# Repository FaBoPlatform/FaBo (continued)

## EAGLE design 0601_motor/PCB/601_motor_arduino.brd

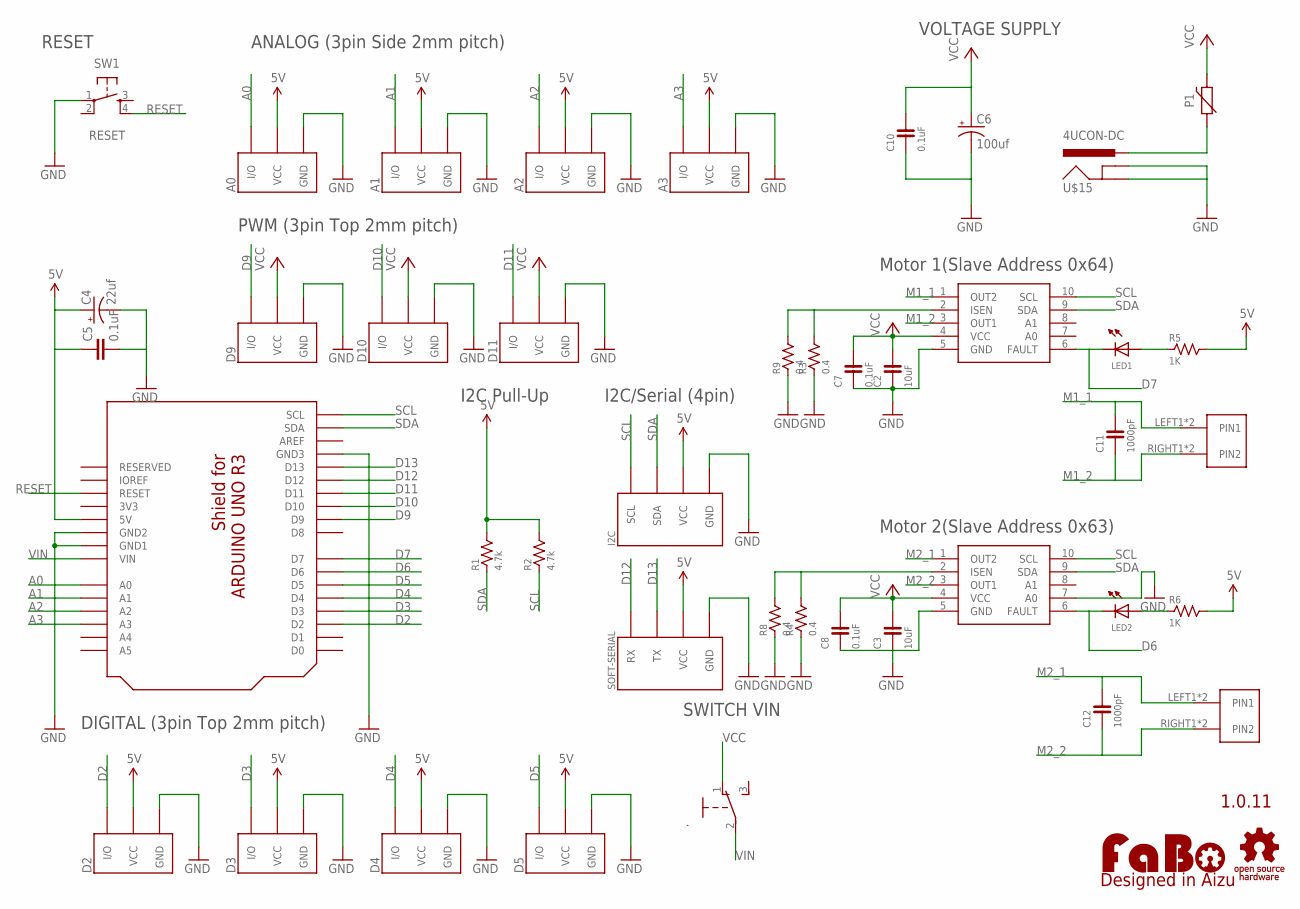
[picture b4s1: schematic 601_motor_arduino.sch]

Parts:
.: SLIDE-EG1218; EG1218
A0, A1, A2, A3: FABO_BRICK_3PIN-S03B-PASK-2; FABO_BRICK_3PIN_S03B-PASK-2
C2, C3: 10uF; 0603
C4: 22uf; 153CLV-0405
C5: 0.1uF; EIA0603
C6: 100uf; 153CLV-0405
C7, C8, C10: 0.1uF; 0603
C11, C12: 1000pF; 0603
D2, D3, D4, D5: FABO_BRICK_3PIN-B03B-PASK-1; FABO_BRICK_3PIN_B03B-PASK-1
D9, D10, D11: FABO_BRICK_3PIN-HEADER; FABO_BRICK_3PIN_HEADER
I2C: FABO_BRICK_I2C-S04B-PASK-2; FABO_BRICK_I2C_S04B-PASK-2
LED1, LED2: LED-0603; 0603
LOGO1: LOGO_FABO-M; LOGO_FABO_M
P1: POLYSWITCHMF-NSML1; 1206
R1, R2: 4.7k; 0603
R3, R4, R8, R9: 0.4; 0603
R5, R6: 1K; 0603
SOFT-SERIAL: FABO_BRICK_SERIAL-S04B-PASK-2; FABO_BRICK_SERIAL_S04B-PASK-2
SW1: RESET; DTS_6_V
U1: ARDUINO_UNO_R3_SHIELD-NOLABEL; ARDUINO_UNO_R3_NOLABEL
U$6: LOGO_OSHW-T_M; LOGO_OSHW_T_MS
U$8, U$10: DRV8830
U$12, U$13: ML-1400-S1
U$15: 4UCON-DC

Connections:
3V3: U1.3V3
5V: A0.VCC, A1.VCC, A2.VCC, A3.VCC, C4.+, C5.1, D2.VCC, D3.VCC, D4.VCC, D5.VCC, I2C.VCC, R1.2, R2.2, R5.2, R6.2, SOFT-SERIAL.VCC, U1.5V
A0: A0.I/O, U1.A0
A1: A1.I/O, U1.A1
A2: A2.I/O, U1.A2
A3: A3.I/O, U1.A3
D2: D2.I/O, U1.D2
D3: D3.I/O, U1.D3
D4: D4.I/O, U1.D4
D5: D5.I/O, U1.D5
D6: LED2.CATHODE, U1.D6, U$10.6 (FAULT)
D7: LED1.CATHODE, U1.D7, U$8.6 (FAULT)
D9: D9.I/O, U1.D9
D10: D10.I/O, U1.D10
D11: D11.I/O, U1.D11
D12: SOFT-SERIAL.RX, U1.D12
D13: SOFT-SERIAL.TX, U1.D13
GND: A0.GND, A1.GND, A2.GND, A3.GND, C2.1, C3.1, C4.-, C5.2, C6.-, C7.1, C8.1, C10.1, D2.GND, D3.GND, D4.GND, D5.GND, D9.GND, D10.GND, D11.GND, I2C.GND, R3.1, R4.1, R8.1, R9.1, SOFT-SERIAL.GND, SW1.1, U1.GND1, U1.GND2, U1.GND3, U$8.5 (GND), U$10.5 (GND), U$10.7 (A0), U$15.GND1 (GND), U$15.GND2 (GNDBREAK)
M1_1: C11.2, U$8.1 (OUT2), U$12.LEFT1 (PIN1), U$12.LEFT2 (PIN1)
M1_2: C11.1, U$8.3 (OUT1), U$12.RIGHT1 (PIN2), U$12.RIGHT2 (PIN2)
M2_1: C12.2, U$10.1 (OUT2), U$13.LEFT1 (PIN1), U$13.LEFT2 (PIN1)
M2_2: C12.1, U$10.3 (OUT1), U$13.RIGHT1 (PIN2), U$13.RIGHT2 (PIN2)
unnamed: P1.P$1 (1), U$15.VCC (PWR)
unnamed: R3.2, R9.2, U$8.2 (ISEN)
unnamed: R4.2, R8.2, U$10.2 (ISEN)
unnamed: LED1.ANODE, R5.1
unnamed: LED2.ANODE, R6.1
RESET: SW1.4, U1.RESET
SCL: I2C.SCL, R2.1, U1.SCL, U$8.10 (SCL), U$10.10 (SCL)
SDA: I2C.SDA, R1.1, U1.SDA, U$8.9 (SDA), U$10.9 (SDA)
VCC: ..1, C2.2, C3.2, C6.+, C7.2, C8.2, C10.2, D9.VCC, D10.VCC, D11.VCC, P1.P$2 (2), U$8.4 (VCC), U$10.4 (VCC)
VIN: ..2, U1.VIN

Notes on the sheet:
1.0.11
I2C/Serial (4pin)
PWM (3pin Top 2mm pitch)
ANALOG (3pin Side 2mm pitch)
I2C Pull-Up
VOLTAGE SUPPLY
DIGITAL (3pin Top 2mm pitch)
RESET
Motor 1(Slave Address 0x64)
Motor 2(Slave Address 0x63)
SWITCH VIN

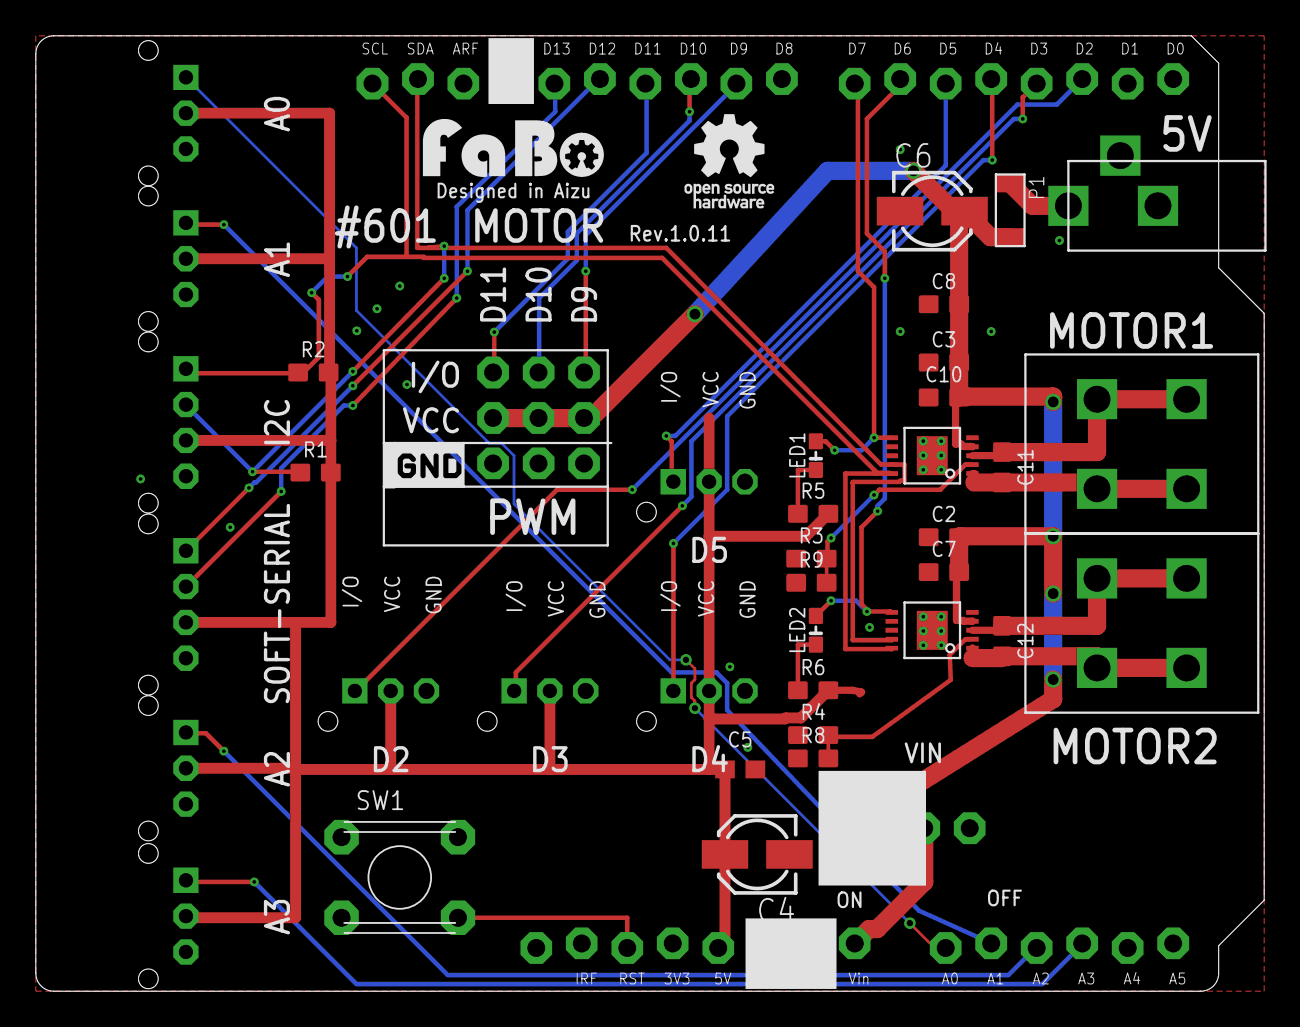
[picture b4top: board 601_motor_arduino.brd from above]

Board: 2 copper layers, 68.6 x 53.3 mm, 45 parts (0 on the bottom side), 31 nets.

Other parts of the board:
U$19: LOGO_SILK_GND

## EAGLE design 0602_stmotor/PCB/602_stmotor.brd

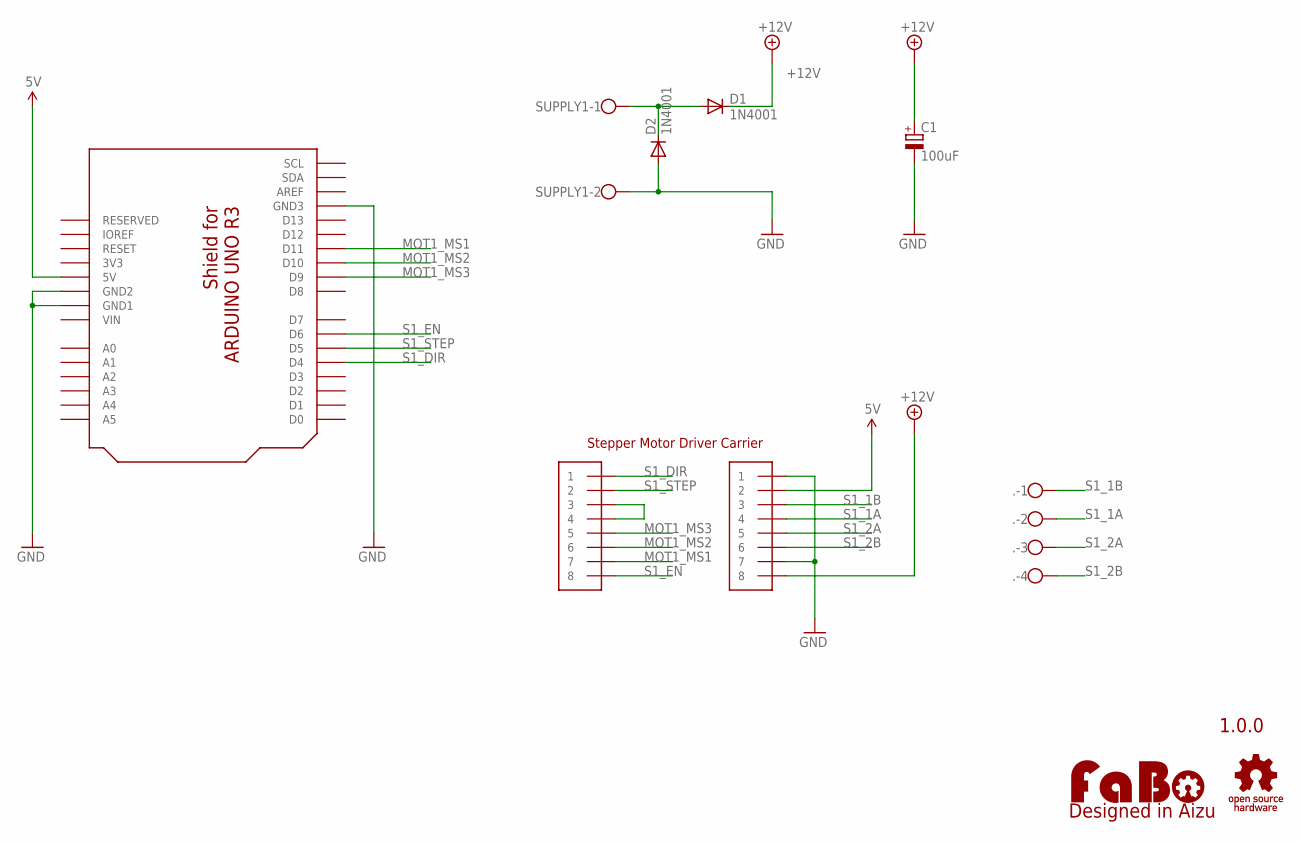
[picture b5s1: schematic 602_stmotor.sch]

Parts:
.: W237-4
C1: 100uF; 153CLV-0807
CN1, CN2: PIN_HEADER_1X8-LONG; PIN_1X8_LONG
D1, D2: 1N4001; DO41-10
LOGO1: LOGO_FABO-M; LOGO_FABO_M
SUPPLY1: W237-102
U1: ARDUINO_UNO_R3_SHIELD-NOLABEL; ARDUINO_UNO_R3_NOLABEL
U$2: LOGO_OSHW-T_M; LOGO_OSHW_T_MS

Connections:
3V3: U1.3V3
5V: CN2.2, U1.5V
+12V: C1.+, CN2.8, D1.C
GND: C1.-, CN2.1, CN2.7, D2.A, SUPPLY1.2, U1.GND1, U1.GND2, U1.GND3
MOT1_MS1: CN1.7, U1.D11
MOT1_MS2: CN1.6, U1.D10
MOT1_MS3: CN1.5, U1.D9
unnamed: D1.A, D2.C, SUPPLY1.1
unnamed: CN1.3, CN1.4
S1_1A: ..2, CN2.4
S1_1B: ..1, CN2.3
S1_2A: ..3, CN2.5
S1_2B: ..4, CN2.6
S1_DIR: CN1.1, U1.D4
S1_EN: CN1.8, U1.D6
S1_STEP: CN1.2, U1.D5
VIN: U1.VIN

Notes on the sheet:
1.0.0
Stepper Motor Driver Carrier

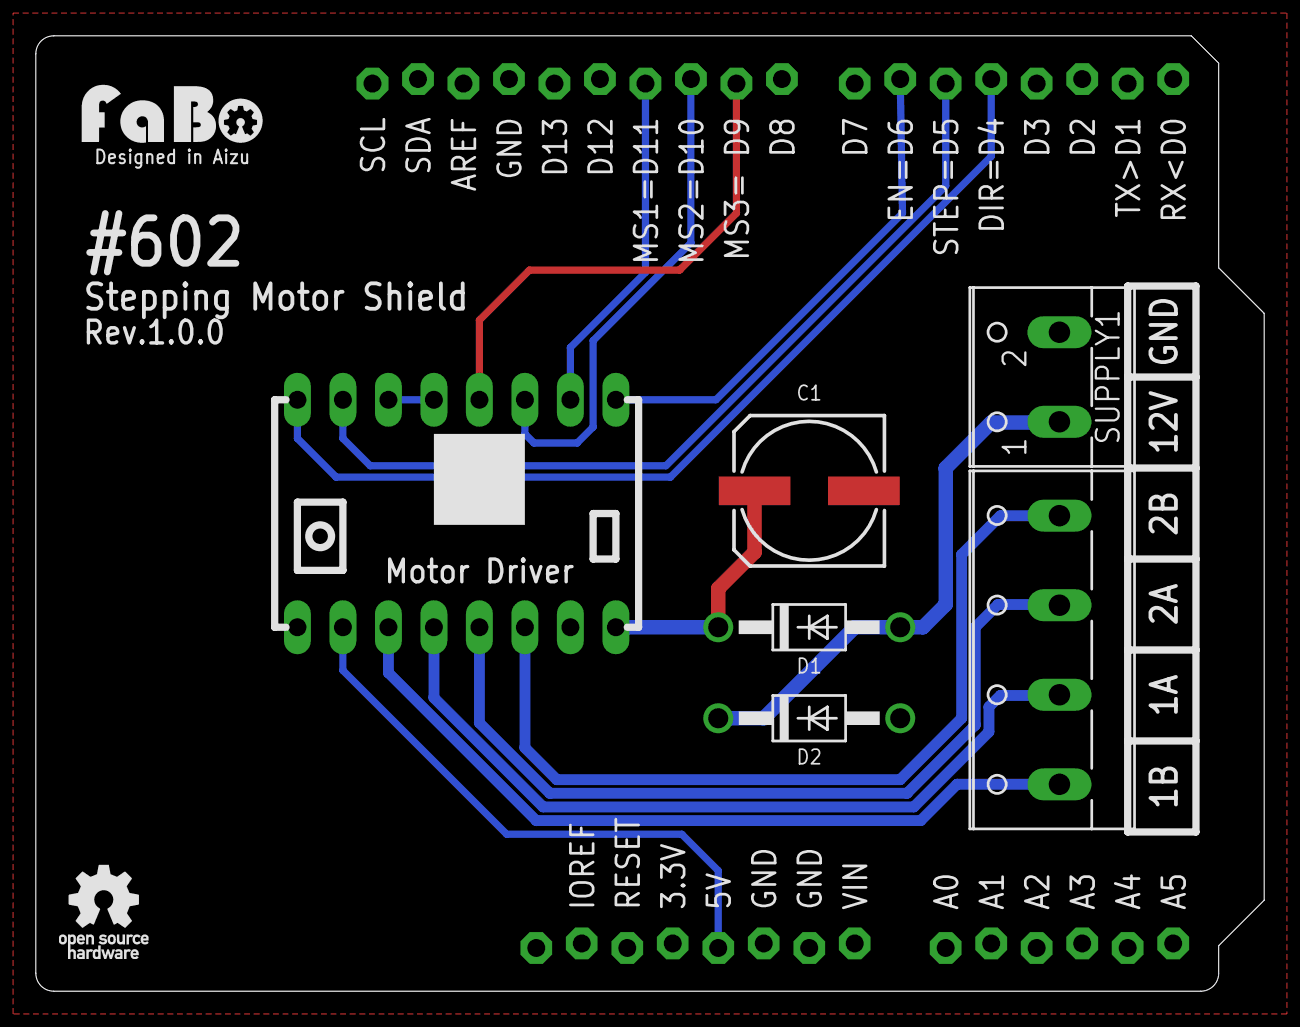
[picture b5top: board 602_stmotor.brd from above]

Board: 2 copper layers, 68.6 x 53.3 mm, 10 parts (0 on the bottom side), 15 nets.

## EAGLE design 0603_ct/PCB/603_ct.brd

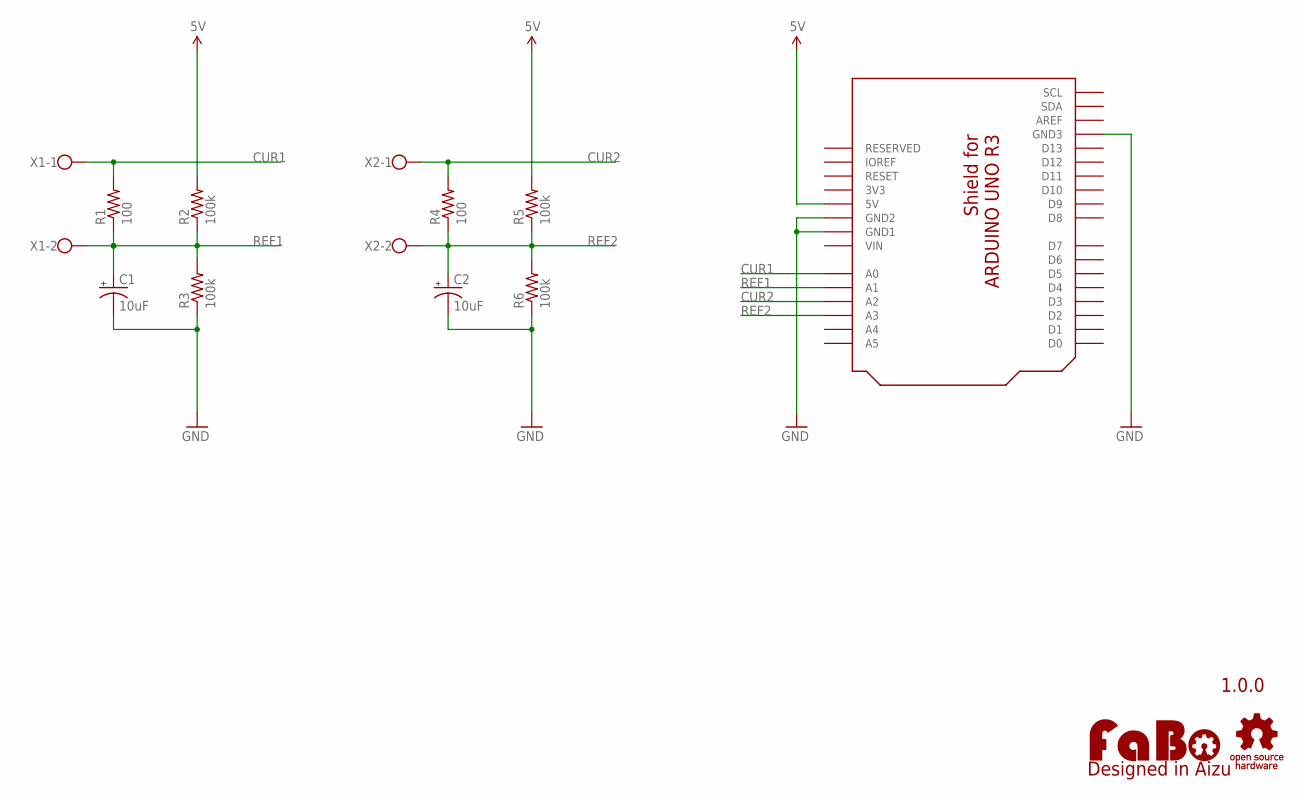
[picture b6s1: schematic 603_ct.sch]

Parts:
C1, C2: 10uF; CAP-POL-AXL-5MM
LOGO1: LOGO_FABO-M; LOGO_FABO_M
R1, R4: 100; RES-AXL-REGULAR
R2, R3, R5, R6: 100k; RES-AXL-REGULAR
U2: ARDUINO_UNO_R3_SHIELD-NOLABEL; ARDUINO_UNO_R3_NOLABEL
U$2: LOGO_OSHW-T_M; LOGO_OSHW_T_MS
X1, X2: W237-102

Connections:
3V3: U2.3V3
5V: R2.P$2 (2), R5.P$2 (2), U2.5V
CUR1: R1.P$2 (2), U2.A0, X1.1
CUR2: R4.P$2 (2), U2.A2, X2.1
GND: C1.-, C2.-, R3.P$1 (1), R6.P$1 (1), U2.GND1, U2.GND2, U2.GND3
REF1: C1.+, R1.P$1 (1), R2.P$1 (1), R3.P$2 (2), U2.A1, X1.2
REF2: C2.+, R4.P$1 (1), R5.P$1 (1), R6.P$2 (2), U2.A3, X2.2
VIN: U2.VIN

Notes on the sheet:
1.0.0

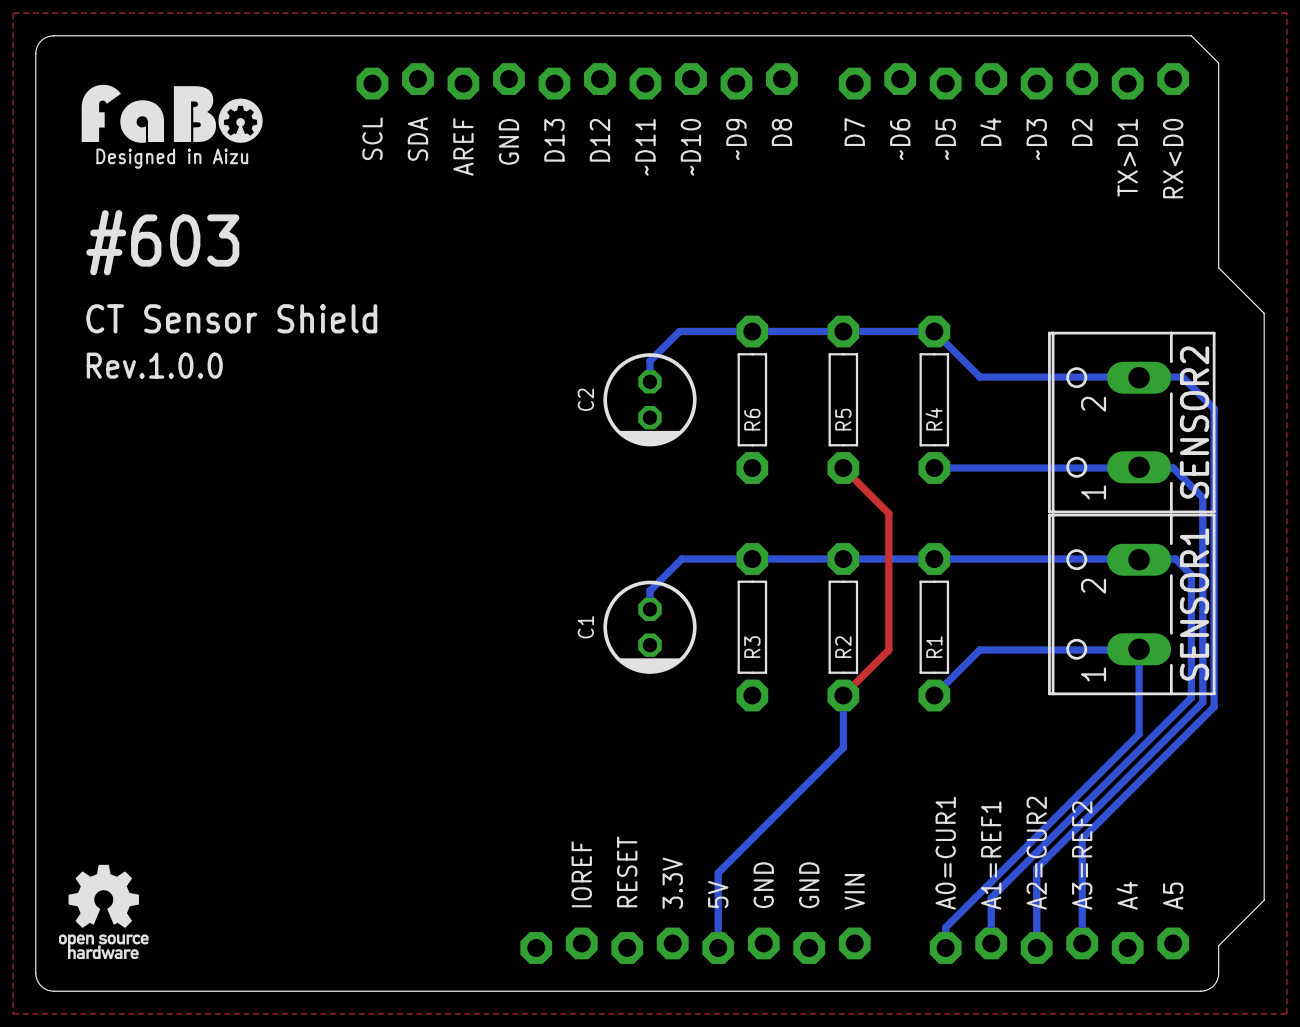
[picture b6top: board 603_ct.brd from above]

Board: 2 copper layers, 68.6 x 53.3 mm, 13 parts (0 on the bottom side), 6 nets.

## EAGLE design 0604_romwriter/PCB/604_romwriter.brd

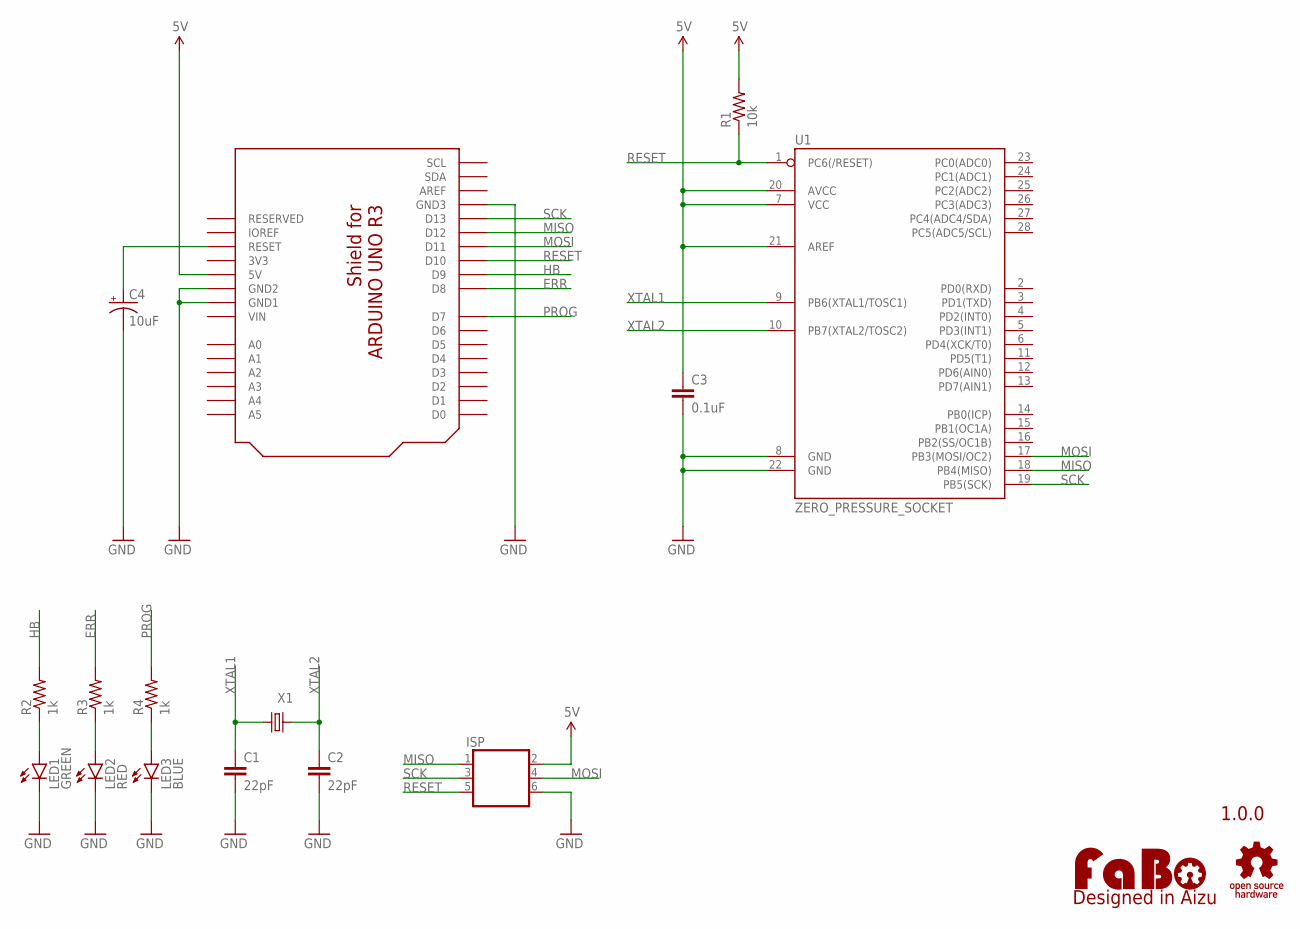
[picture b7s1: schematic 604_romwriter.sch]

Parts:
C1, C2: 22pF; CAP-PTH-SMALL
C3: 0.1uF; CAP-PTH-SMALL
C4: 10uF; CAP-POL-AXL-5MM
ISP: PINHEAD_2X3; PIN_2X3
LED1: GREEN; LED-5MM
LED2: RED; LED-5MM
LED3: BLUE; LED-5MM
LOGO1: LOGO_FABO-M; LOGO_FABO_M
R1: 10k; RES-AXL-REGULAR
R2, R3, R4: 1k; RES-AXL-REGULAR
U1: ZERO_PRESSURE_SOCKET; ZERO_PRESSURE_SOCKET_DIL28
U2: ARDUINO_UNO_R3_SHIELD-NOLABEL; ARDUINO_UNO_R3_NOLABEL
U$2: LOGO_OSHW-T_M; LOGO_OSHW_T_MS
X1: CRYSTAL; RESONATOR_PTH

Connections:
3V3: U2.3V3
5V: C3.1, ISP.2, R1.P$2 (2), U1.7 (VCC), U1.20 (AVCC), U1.21 (AREF), U2.5V
ERR: R3.P$2 (2), U2.D8
GND: C1.2, C2.2, C3.2, C4.-, ISP.6, LED1.K (C), LED2.K (C), LED3.K (C), U1.8 (GND), U1.22 (GND), U2.GND1, U2.GND2, U2.GND3
HB: R2.P$2 (2), U2.D9
MISO: ISP.1, U1.18 (PB4(MISO)), U2.D12
MOSI: ISP.4, U1.17 (PB3(MOSI/OC2)), U2.D11
unnamed: C4.+, U2.RESET
unnamed: LED1.A, R2.P$1 (1)
unnamed: LED2.A, R3.P$1 (1)
unnamed: LED3.A, R4.P$1 (1)
PROG: R4.P$2 (2), U2.D7
RESET: ISP.5, R1.P$1 (1), U1.1 (PC6(/RESET)), U2.D10
SCK: ISP.3, U1.19 (PB5(SCK)), U2.D13
VIN: U2.VIN
XTAL1: C1.1, U1.9 (PB6(XTAL1/TOSC1)), X1.1
XTAL2: C2.1, U1.10 (PB7(XTAL2/TOSC2)), X1.2

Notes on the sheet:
1.0.0

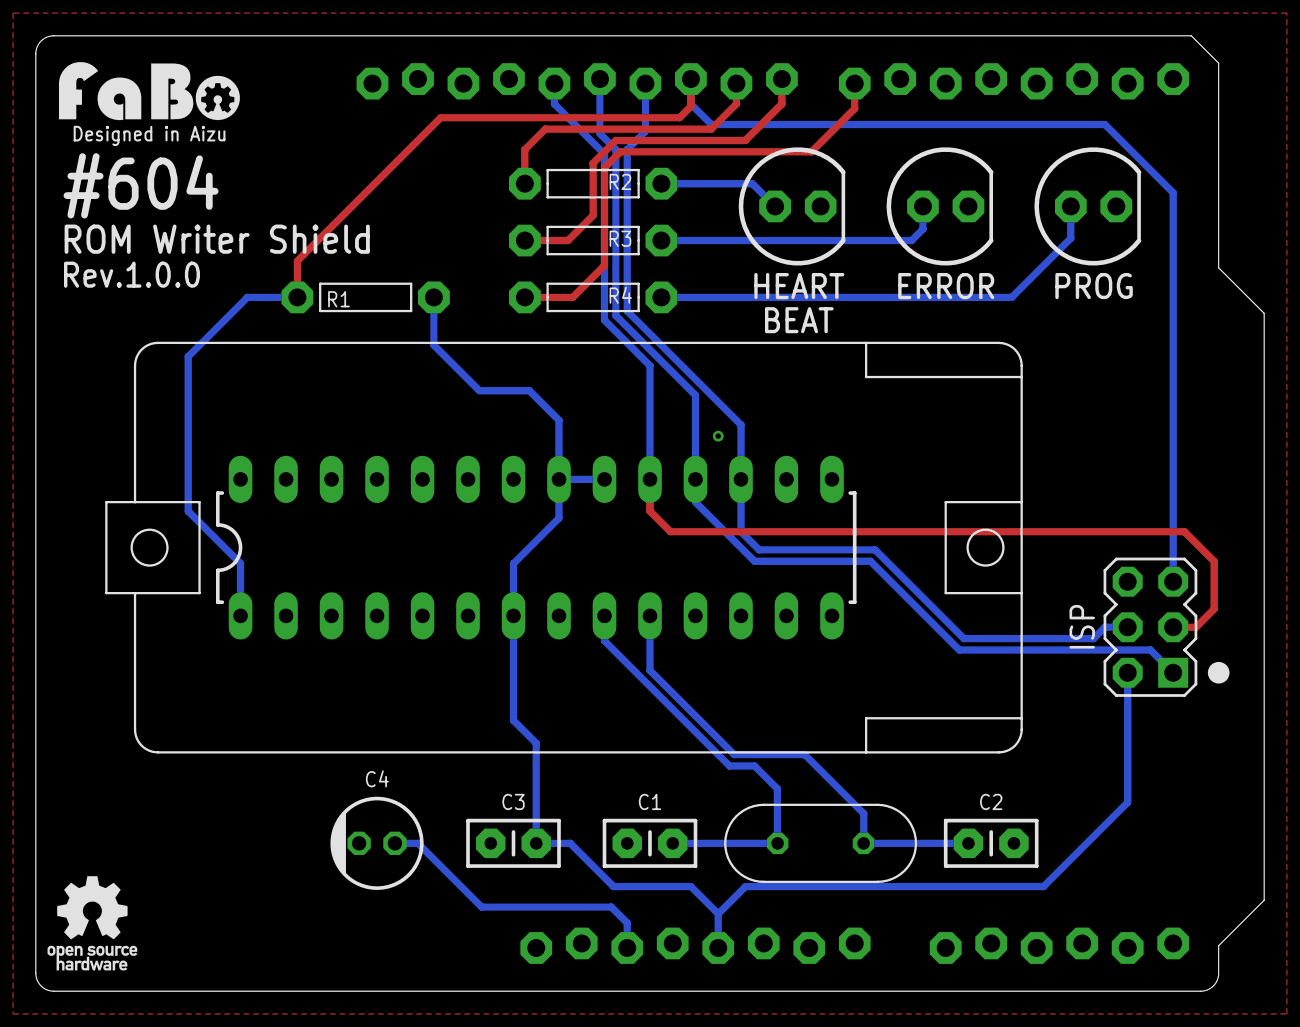
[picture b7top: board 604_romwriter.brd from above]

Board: 2 copper layers, 68.6 x 53.3 mm, 17 parts (0 on the bottom side), 15 nets.

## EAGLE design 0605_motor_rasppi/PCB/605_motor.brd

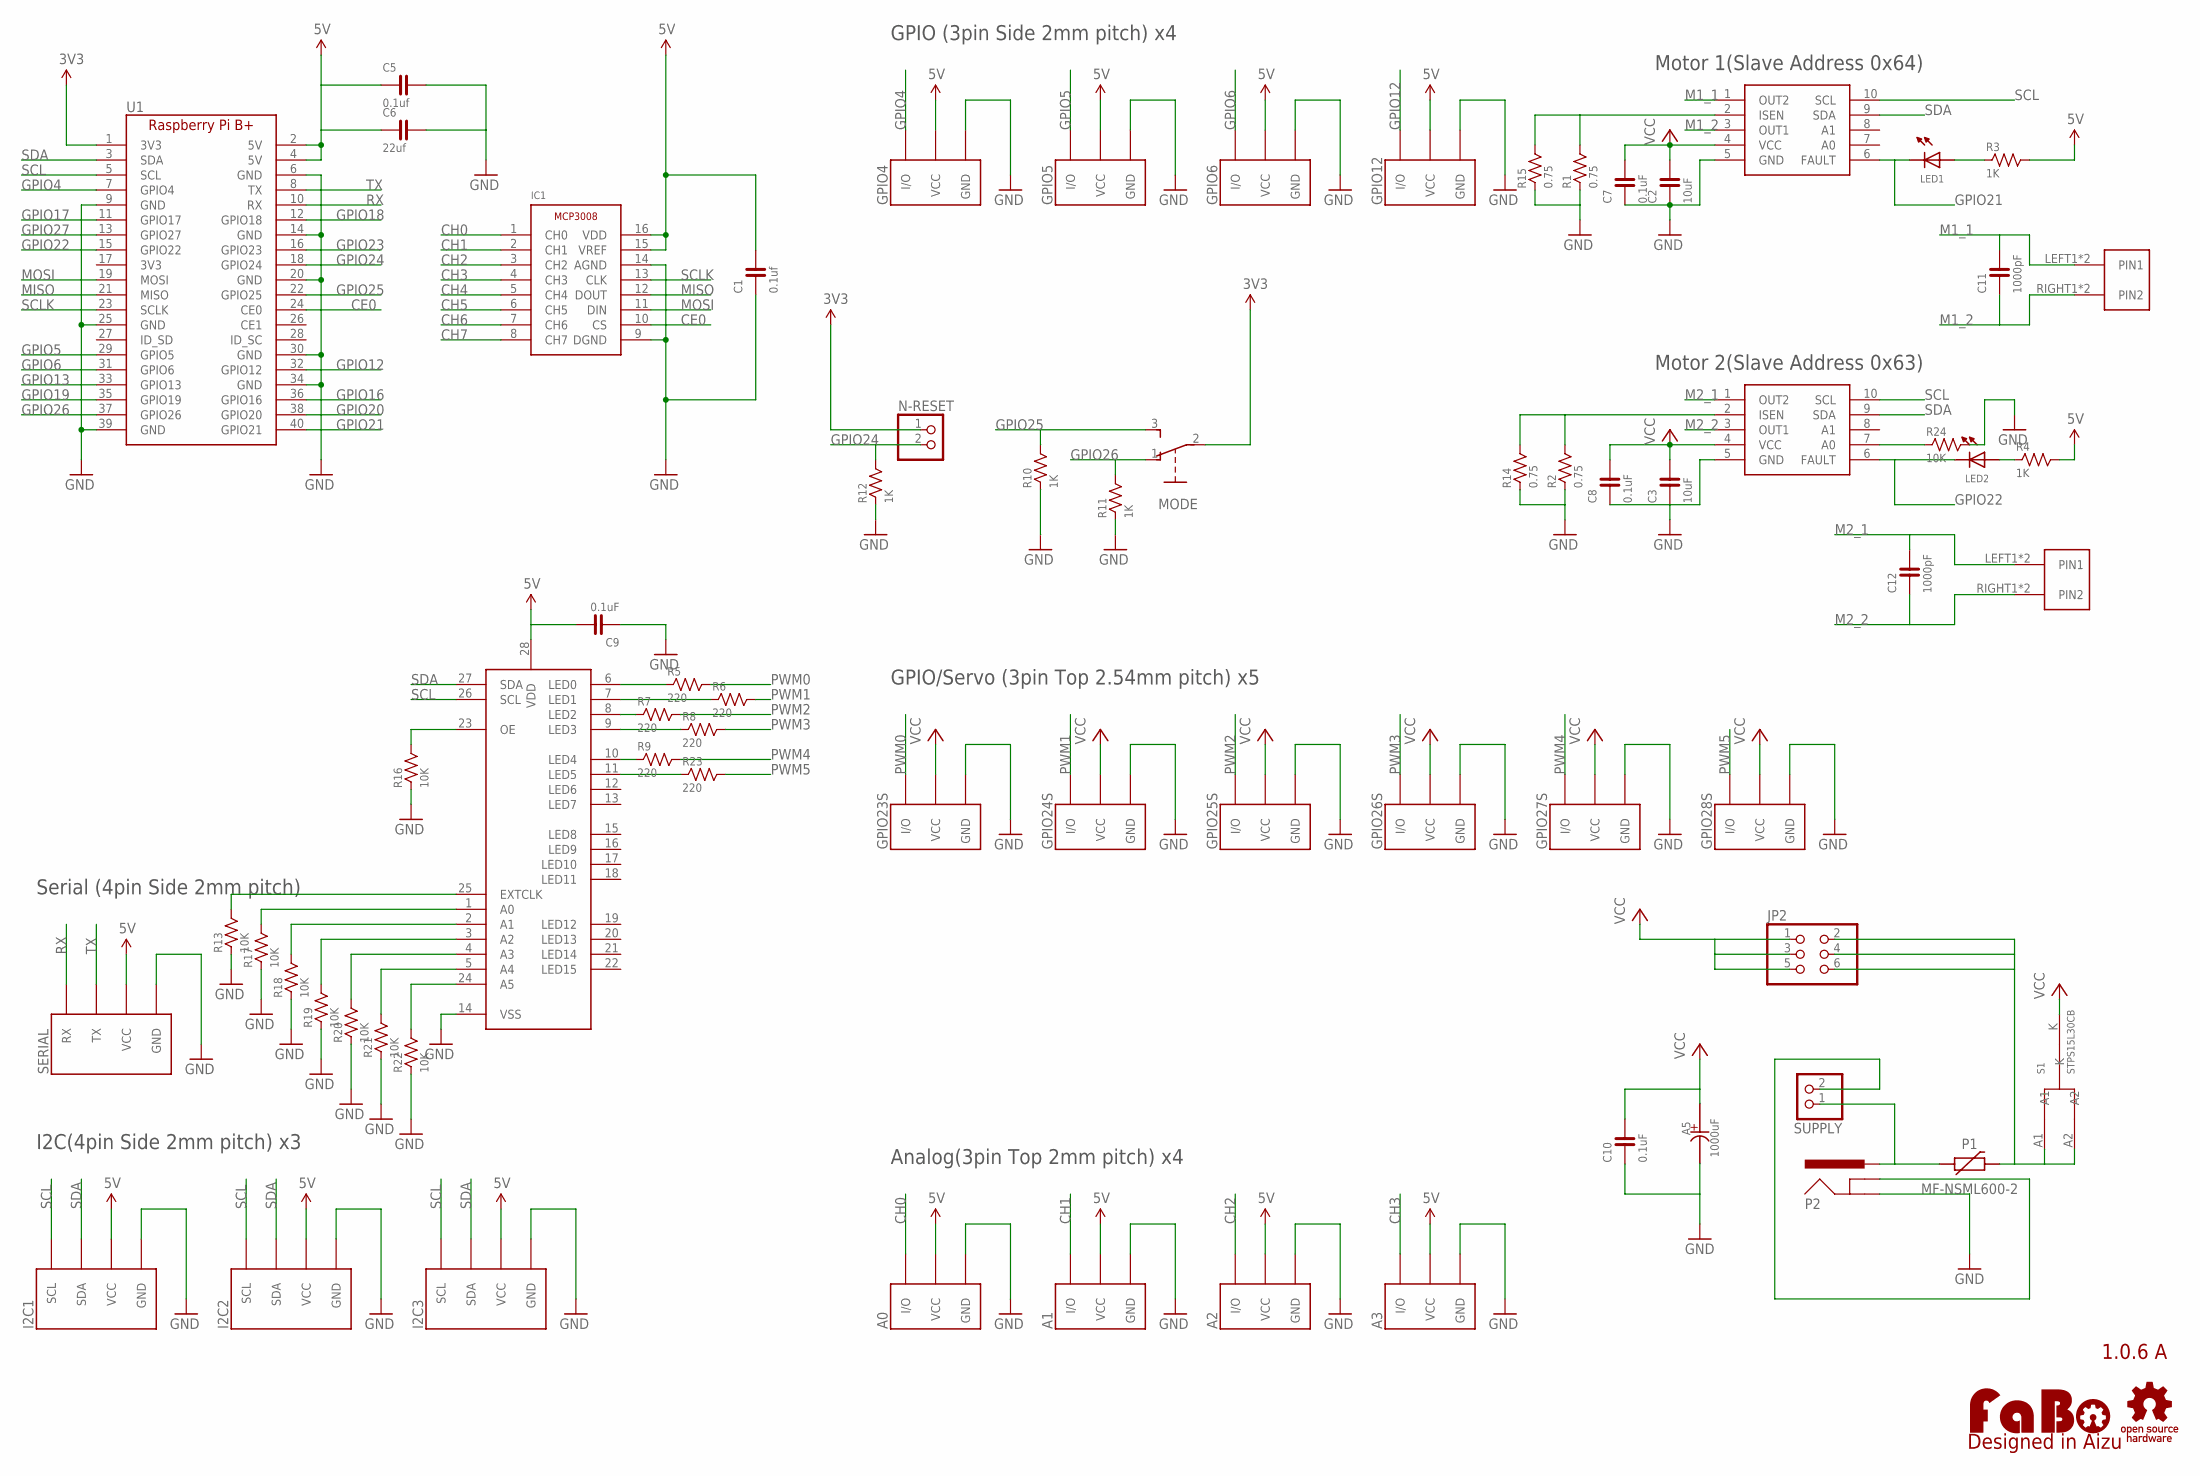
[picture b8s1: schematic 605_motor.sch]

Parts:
A0, A1, A2, A3: FABO_BRICK_3PIN-B03B-PASK-1; FABO_BRICK_3PIN_B03B-PASK-1
A5: 1000uF; D12.5
C1, C5: 0.1uf; 0603
C2, C3: 10uF; 0603
C6: 22uf; 0603
C7, C8, C9, C10: 0.1uF; 0603
C11, C12: 1000pF; 0603
GPIO4, GPIO5, GPIO6, GPIO12: FABO_BRICK_3PIN-S03B-PASK-2; FABO_BRICK_3PIN_S03B-PASK-2
GPIO23S, GPIO24S, GPIO25S, GPIO26S, GPIO27S, GPIO28S: FABO_BRICK_3PIN-HEADER; FABO_BRICK_3PIN_HEADER
I2C1, I2C2, I2C3: FABO_BRICK_I2C-S04B-PASK-2; FABO_BRICK_I2C_S04B-PASK-2
IC1: MICROCHIP-MCP3008
JP2: PINHD-2X3; 2X03
LED1, LED2: LED-0603; 0603
LOGO1: LOGO_FABO-M; LOGO_FABO_M
MODE: SLIDE-EG1218; EG1218
N-RESET: PINHD-1X2; 1X02
P1: MF-NSML600-2; 1206
P2: DC-JACKM04339A0; M04339A0
R1, R2, R14, R15: 0.75; 0603
R3, R4, R10, R11, R12: 1K; 0603
R5, R6, R7, R8, R9, R23: 220; 0603
R13, R22: 10K; 0402
R16, R17, R18, R19, R20, R21, R24: 10K; 0603
S1: STPS15L30CB; STPS15L30C
SERIAL: FABO_BRICK_SERIAL-S04B-PASK-2; FABO_BRICK_SERIAL_S04B-PASK-2
SUPPLY: PINHD-1X2; 1X02
U1: RASPBERRY_PI_B+
U$4: LOGO_OSHW-M; LOGO_OSHW_M
U$8, U$10: DRV8830
U$9: PCA9685
U$12, U$13: ML-1400-S1

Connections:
3V3: MODE.2, N-RESET.1, U1.1 (3V3)
5V: A0.VCC, A1.VCC, A2.VCC, A3.VCC, C1.2, C5.1, C6.1, C9.2, GPIO4.VCC, GPIO5.VCC, GPIO6.VCC, GPIO12.VCC, I2C1.VCC, I2C2.VCC, I2C3.VCC, IC1.15 (VREF), IC1.16 (VDD), R3.2, R4.2, SERIAL.VCC, U1.2 (5V), U1.4 (5V), U$9.28 (VDD)
CE0: IC1.10 (CS), U1.24 (CE0)
CH0: A0.I/O, IC1.1 (CH0)
CH1: A1.I/O, IC1.2 (CH1)
CH2: A2.I/O, IC1.3 (CH2)
CH3: A3.I/O, IC1.4 (CH3)
CH4: IC1.5 (CH4)
CH5: IC1.6 (CH5)
CH6: IC1.7 (CH6)
CH7: IC1.8 (CH7)
GND: A0.GND, A1.GND, A2.GND, A3.GND, A5.-, C1.1, C2.1, C3.1, C5.2, C6.2, C7.1, C8.1, C9.1, C10.1, GPIO4.GND, GPIO5.GND, GPIO6.GND, GPIO12.GND, GPIO23S.GND, GPIO24S.GND, GPIO25S.GND, GPIO26S.GND, GPIO27S.GND, GPIO28S.GND, I2C1.GND, I2C2.GND, I2C3.GND, IC1.9 (DGND), IC1.14 (AGND), P2.GND, R1.1, R2.1, R10.1, R11.1, R12.1, R13.P$1 (1), R14.1, R15.1, R16.1, R17.1, R18.1, R19.1, R20.1, R21.1, R22.P$1 (1), R24.2, SERIAL.GND, U1.6 (GND), U1.9 (GND), U1.14 (GND), U1.20 (GND), U1.25 (GND), U1.30 (GND), U1.34 (GND), U1.39 (GND), U$8.5 (GND), U$9.14 (VSS), U$10.5 (GND)
GPIO4: GPIO4.I/O, U1.7 (GPIO4)
GPIO5: GPIO5.I/O, U1.29 (GPIO5)
GPIO6: GPIO6.I/O, U1.31 (GPIO6)
GPIO12: GPIO12.I/O, U1.32 (GPIO12)
GPIO13: U1.33 (GPIO13)
GPIO16: U1.36 (GPIO16)
GPIO17: U1.11 (GPIO17)
GPIO18: U1.12 (GPIO18)
GPIO19: U1.35 (GPIO19)
GPIO20: U1.38 (GPIO20)
GPIO21: LED1.CATHODE, U1.40 (GPIO21), U$8.6 (FAULT)
GPIO22: LED2.CATHODE, U1.15 (GPIO22), U$10.6 (FAULT)
GPIO23: U1.16 (GPIO23)
GPIO24: N-RESET.2, R12.2, U1.18 (GPIO24)
GPIO25: MODE.3, R10.2, U1.22 (GPIO25)
GPIO26: MODE.1, R11.2, U1.37 (GPIO26)
GPIO27: U1.13 (GPIO27)
LED0: R5.1, U$9.6 (LED0)
LED1: R6.1, U$9.7 (LED1)
LED2: R7.1, U$9.8 (LED2)
LED3: R8.1, U$9.9 (LED3)
LED4: R9.1, U$9.10 (LED4)
LED5: R23.1, U$9.11 (LED5)
M1_1: C11.2, U$8.1 (OUT2), U$12.LEFT1 (PIN1), U$12.LEFT2 (PIN1)
M1_2: C11.1, U$8.3 (OUT1), U$12.RIGHT1 (PIN2), U$12.RIGHT2 (PIN2)
M2_1: C12.2, U$10.1 (OUT2), U$13.LEFT1 (PIN1), U$13.LEFT2 (PIN1)
M2_2: C12.1, U$10.3 (OUT1), U$13.RIGHT1 (PIN2), U$13.RIGHT2 (PIN2)
MISO: IC1.12 (DOUT), U1.21 (MISO)
MOSI: IC1.11 (DIN), U1.19 (MOSI)
unnamed: R1.2, R15.2, U$8.2 (ISEN)
unnamed: R2.2, R14.2, U$10.2 (ISEN)
unnamed: LED1.ANODE, R3.1
unnamed: P1.P$1 (1), P2.VCC (PWR), SUPPLY.1
unnamed: LED2.ANODE, R4.1
unnamed: R16.2, U$9.23 (OE)
unnamed: R13.P$2 (2), U$9.25 (EXTCLK)
unnamed: R17.2, U$9.1 (A0)
unnamed: R18.2, U$9.2 (A1)
unnamed: R19.2, U$9.3 (A2)
unnamed: R20.2, U$9.4 (A3)
unnamed: R21.2, U$9.5 (A4)
unnamed: R22.P$2 (2), U$9.24 (A5)
unnamed: JP2.2, JP2.4, JP2.6, P1.P$2 (2), S1.A1, S1.A2
unnamed: R24.1, U$10.7 (A0)
unnamed: P2.GNDBREAK, SUPPLY.2
PWM0: GPIO23S.I/O, R5.2
PWM1: GPIO24S.I/O, R6.2
PWM2: GPIO25S.I/O, R7.2
PWM3: GPIO26S.I/O, R8.2
PWM4: GPIO27S.I/O, R9.2
PWM5: GPIO28S.I/O, R23.2
RX: SERIAL.RX, U1.10 (RX)
SCL: I2C1.SCL, I2C2.SCL, I2C3.SCL, U1.5 (SCL), U$8.10 (SCL), U$9.26 (SCL), U$10.10 (SCL)
SCLK: IC1.13 (CLK), U1.23 (SCLK)
SDA: I2C1.SDA, I2C2.SDA, I2C3.SDA, U1.3 (SDA), U$8.9 (SDA), U$9.27 (SDA), U$10.9 (SDA)
TX: SERIAL.TX, U1.8 (TX)
VCC: A5.+, C2.2, C3.2, C7.2, C8.2, C10.2, GPIO23S.VCC, GPIO24S.VCC, GPIO25S.VCC, GPIO26S.VCC, GPIO27S.VCC, GPIO28S.VCC, JP2.1, JP2.3, JP2.5, S1.K, U$8.4 (VCC), U$10.4 (VCC)

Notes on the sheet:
1.0.6 A
GPIO (3pin Side 2mm pitch) x4
I2C(4pin Side 2mm pitch) x3
Serial (4pin Side 2mm pitch)
GPIO/Servo (3pin Top 2.54mm pitch) x5
Analog(3pin Top 2mm pitch) x4
Motor 1(Slave Address 0x64)
Motor 2(Slave Address 0x63)

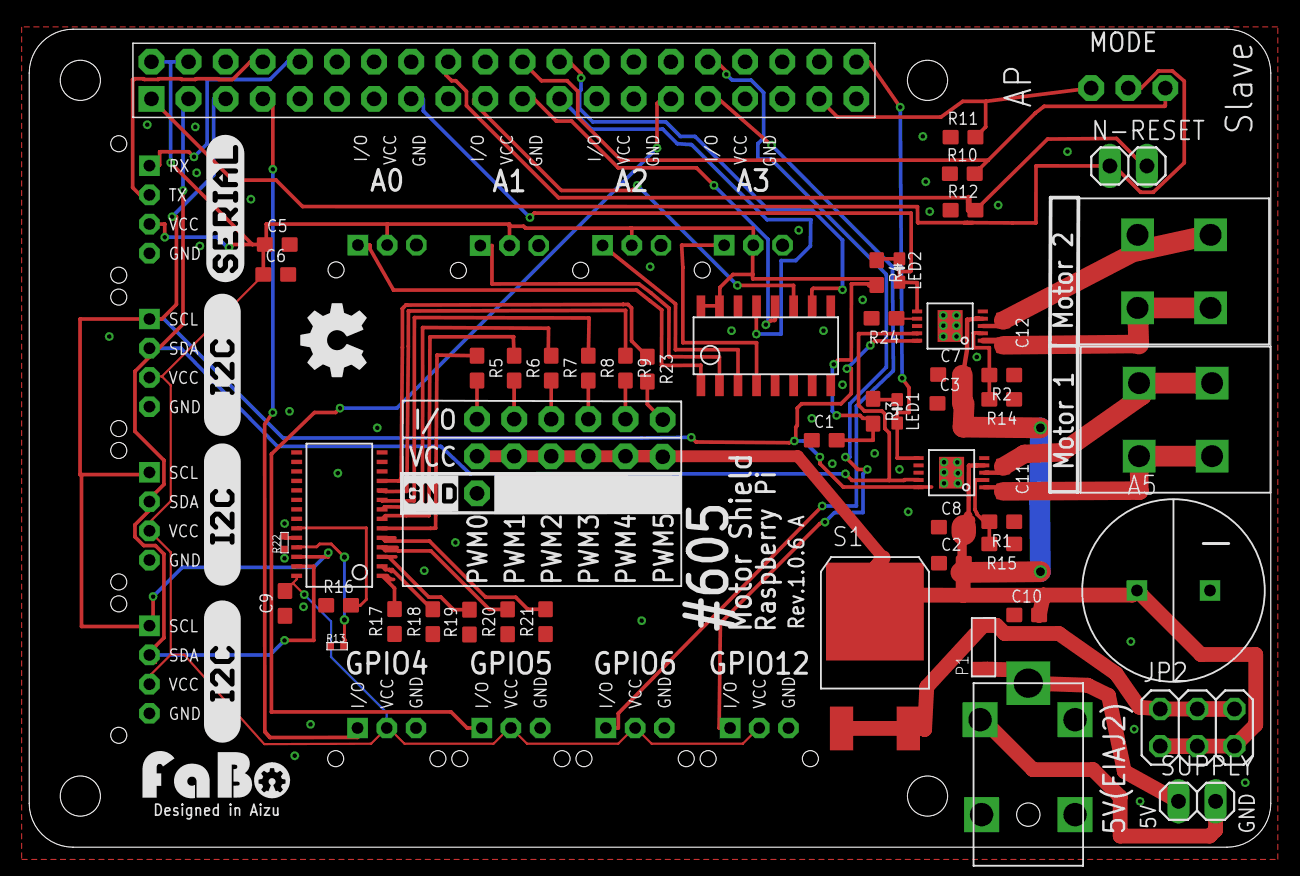
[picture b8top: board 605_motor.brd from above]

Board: 2 copper layers, 85.0 x 56.0 mm, 77 parts (0 on the bottom side), 57 nets.

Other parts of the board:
U$2, U$5, U$6: LOGO_SILK_I2C
U$3: LOGO_SILK_SERIAL2
U$7: LOGO_SILK_GND
